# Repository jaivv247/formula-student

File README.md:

# formula-student
Jais formula student stuff

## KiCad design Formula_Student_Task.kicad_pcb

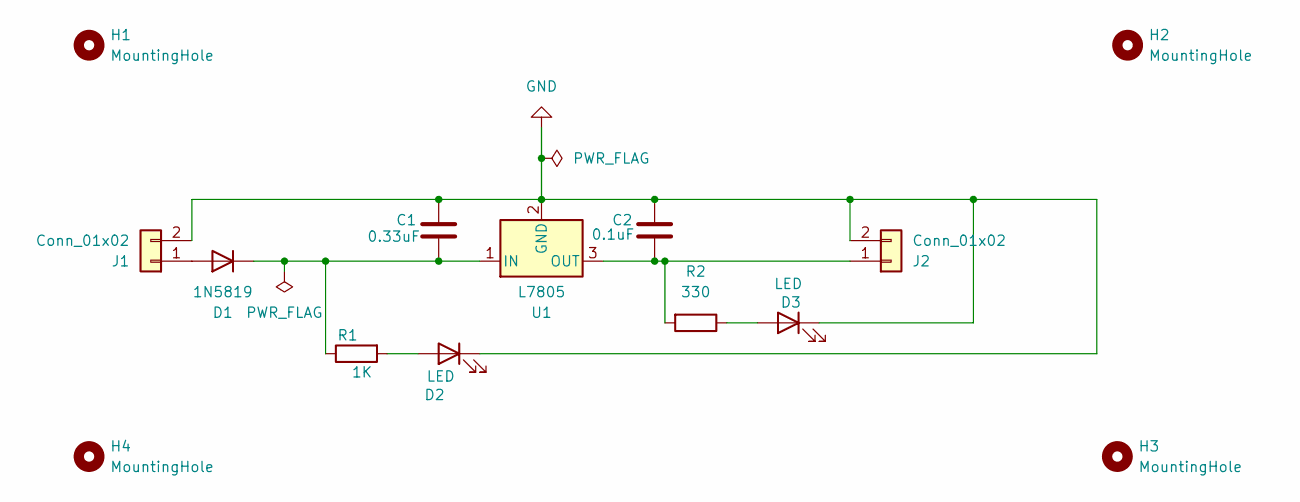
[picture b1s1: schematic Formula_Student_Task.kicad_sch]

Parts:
C1: 0.33uF; C_Disc_D10.0mm_W2.5mm_P5.00mm
C2: 0.1uF; C_Disc_D10.0mm_W2.5mm_P5.00mm
D1: 1N5819; D_DO-41_SOD81_P10.16mm_Horizontal
D2, D3: LED; D_5W_P5.08mm_Vertical_AnodeUp
H1, H2, H3, H4: MountingHole; MountingHole_3.2mm_M3
J1, J2: Conn_01x02; JWT_A3963_1x02_P3.96mm_Vertical
R1: 1K; R_Axial_DIN0204_L3.6mm_D1.6mm_P1.90mm_Vertical
R2: 330; R_Axial_DIN0204_L3.6mm_D1.6mm_P1.90mm_Vertical
U1: L7805; TO-220-3_Vertical

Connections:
GND: C1.1, C2.1, D2.1 (K), D3.1 (K), J1.2 (GND), J2.2 (GND), U1.2 (GND)
unnamed: D1.2 (A), J1.1 (12V)
unnamed: C1.2, D1.1 (K), R1.1, U1.1 (IN)
unnamed: D2.2 (A), R1.2
unnamed: D3.2 (A), R2.1
unnamed: C2.2, J2.1 (5V), R2.2, U1.3 (OUT)

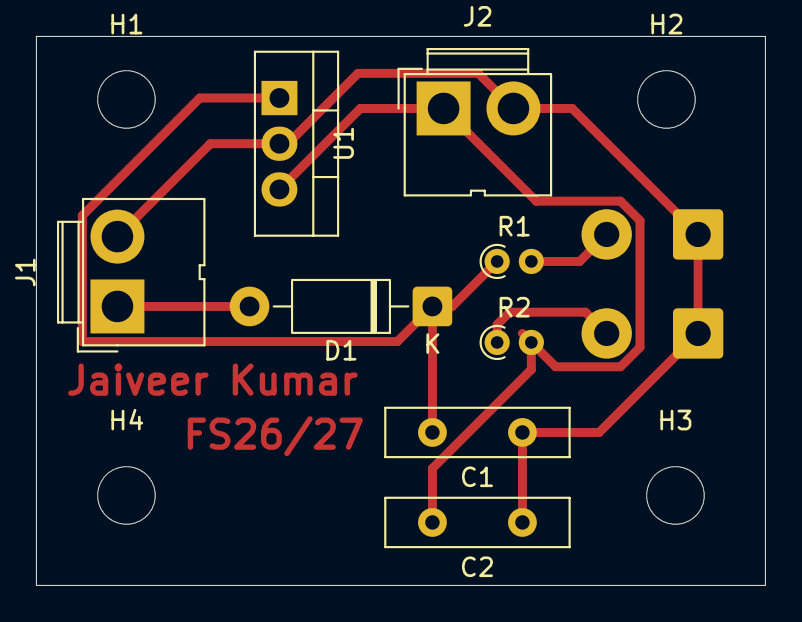
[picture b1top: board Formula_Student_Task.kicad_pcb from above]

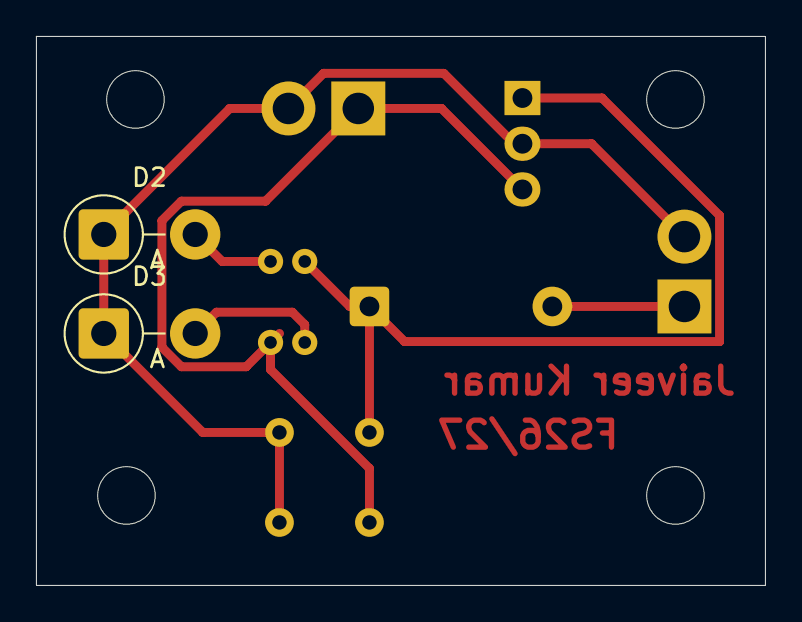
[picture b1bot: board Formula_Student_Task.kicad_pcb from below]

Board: 2 copper layers, 40.5 x 30.5 mm, 14 parts (2 on the bottom side), 6 nets.
